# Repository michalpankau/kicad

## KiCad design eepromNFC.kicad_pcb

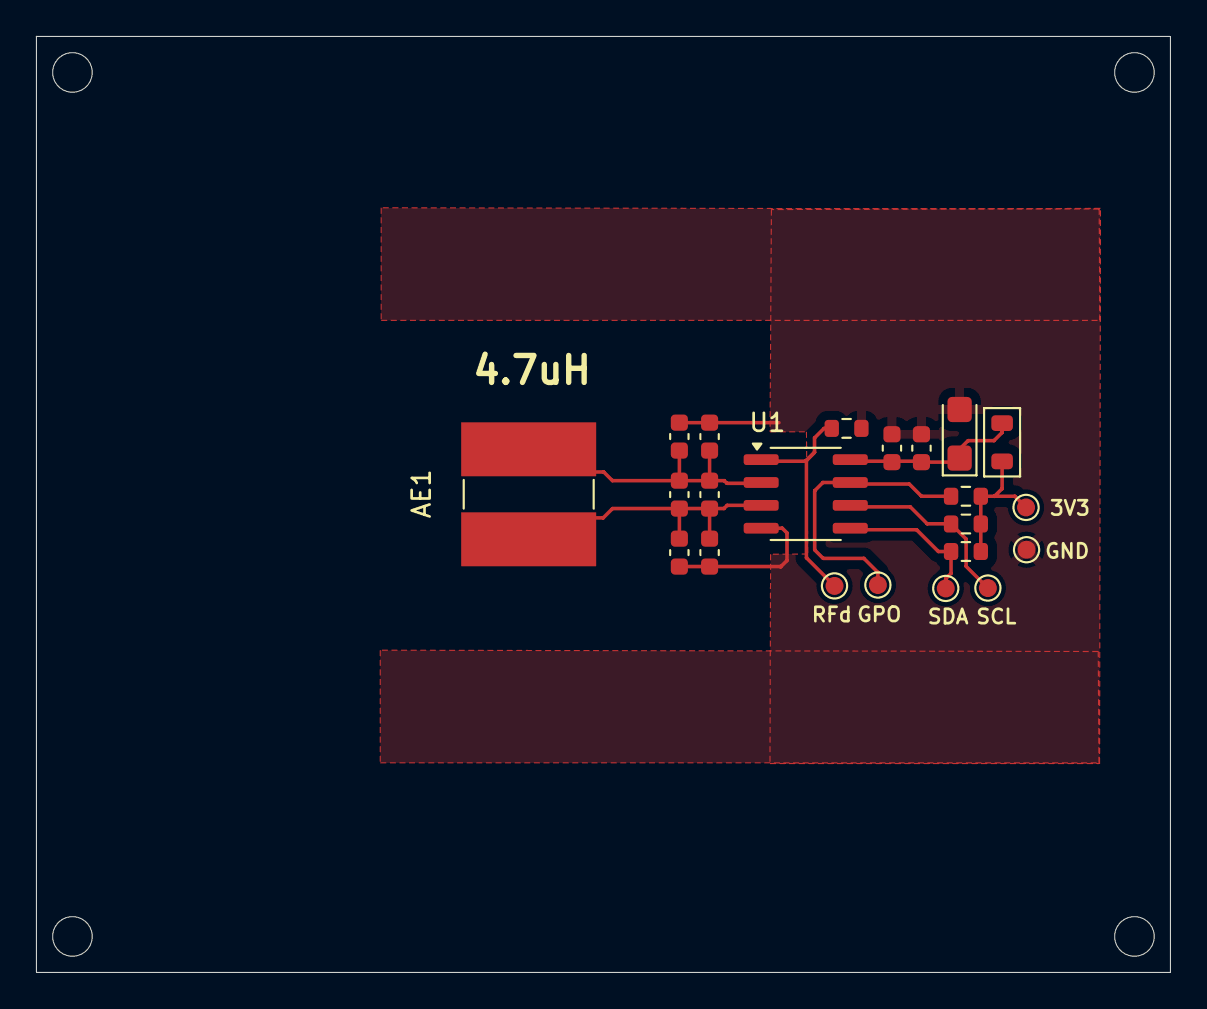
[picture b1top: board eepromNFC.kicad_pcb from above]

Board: 2 copper layers, 63.0 x 52.0 mm, 26 parts (0 on the bottom side), 9 nets.

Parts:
3V3: TestPoint_Pad_D1.0mm
AE1: Antenna_Loop; L_Ferrocore_DLG-0703
C1: 1u; CP_EIA-3216-18_Kemet-A
C2: 100n; C_0603_1608Metric
C3: 100p; C_0603_1608Metric
C4, C5, C6, C7, C8, C9: C; C_0603_1608Metric
GND: TestPoint_Pad_D1.0mm
GPO: TestPoint_Pad_D1.0mm
H1, H1#2, H1#3, H1#4: MountingHole_2.2mm_M2_ISO7380
L1: 600ohm; Ferrite_0805_2012Metric
R1, R2, R3, R4: 4k7; R_0603_1608Metric
RFd: TestPoint_Pad_D1.0mm
SCL: TestPoint_Pad_D1.0mm
SDA: TestPoint_Pad_D1.0mm
U1: M24SR02-Y; SOIC-8_3.9x4.9mm_P1.27mm

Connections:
/3V3: 3V3.2, L1.1, R1.1, R2.1, R3.1
/GND: C1.2, C2.2, C3.2, C4.2, C5.2, C6.2, C7.2, GND.1, R4.2, U1.4 (VSS)
/GPO: GPO.5, R3.2, U1.7 (GPO)
/RFd: R4.1, RFd.6, U1.1 (RFdis)
/SCL: R2.2, SCL.4, U1.6 (SCL)
/SDA: R1.2, SDA.3, U1.5 (SDA)
unnamed: AE1.1, C4.1, C5.1, C8.1, C9.1, U1.2 (AC0)
unnamed: AE1.2, C6.1, C7.1, C8.2, C9.2, U1.3 (AC1)
unnamed: C1.1, C2.1, C3.1, L1.2, U1.8 (VCC)
